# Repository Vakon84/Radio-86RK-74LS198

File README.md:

# SN74198N (K155IR13) replacement

SN74198 (K155IR13) replacement with a pair of 74LS194D

Radio-86RK, a 8080-based home computer from 1986, uses a SN74198 parallel-in, serial-out shift register to serialize pixel data for the composite video output. The part is long obsolete. Although it can still be found on eBay, etc., a fully functional replacement can easily be built from two 74LS194 shift registers. Using the 74LS194D in SOIC packages, it is possible to built a size- and pin-compatible replacement for 74198.

## Schematic and PCB layout
[Schematic](Eagle/74LS198-schematic.pdf)

[PCB layout](Eagle/74LS198-pcb.pdf)

## Bill of Materials

Device   | Package | Quantity
-------- | ------- | --------
74LS194D | SOIC-16 | 2
Capacitor 0.1uF | 0805 | 2

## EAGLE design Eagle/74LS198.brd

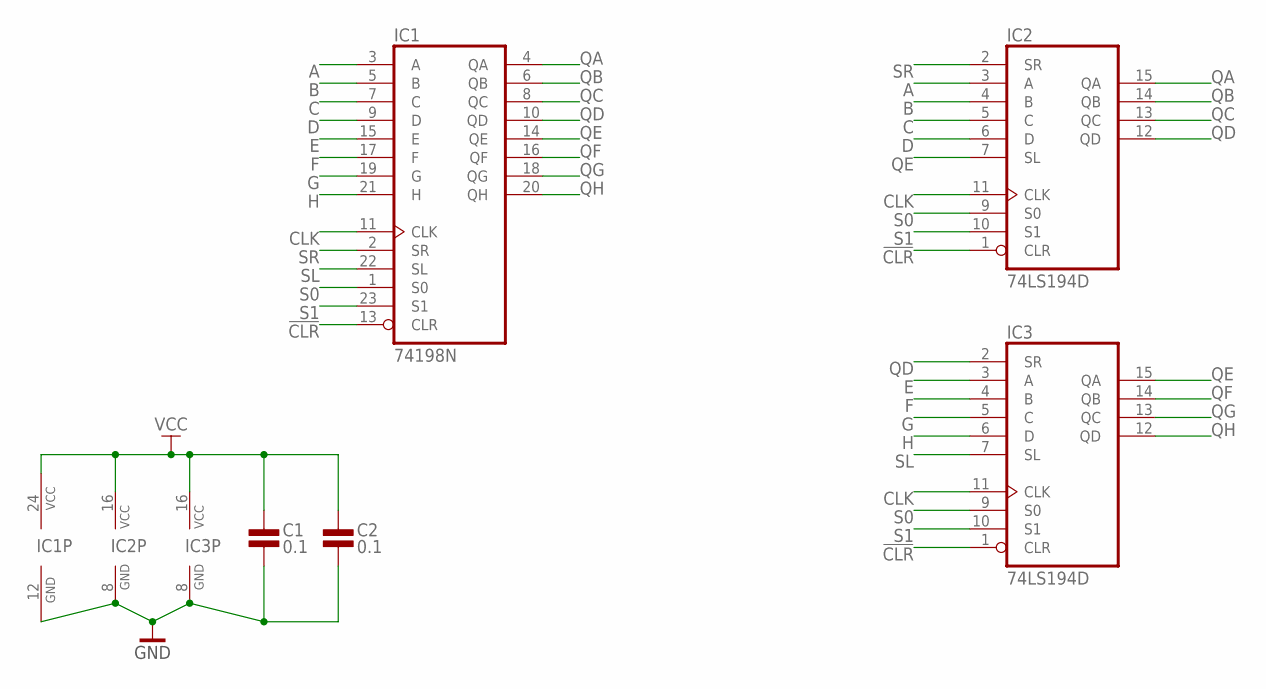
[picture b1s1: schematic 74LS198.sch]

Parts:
C1, C2: 0.1; 0805
IC1: 74198N; DIP24W
IC2, IC3: 74LS194D; SO16

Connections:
!CLR: IC1.13 (CLR), IC2.1 (CLR), IC3.1 (CLR)
A: IC1.3 (A), IC2.3 (A)
B: IC1.5 (B), IC2.4 (B)
C: IC1.7 (C), IC2.5 (C)
CLK: IC1.11 (CLK), IC2.11 (CLK), IC3.11 (CLK)
D: IC1.9 (D), IC2.6 (D)
E: IC1.15 (E), IC3.3 (A)
F: IC1.17 (F), IC3.4 (B)
G: IC1.19 (G), IC3.5 (C)
GND: C1.1, C2.1, IC1.12 (GND), IC2.8 (GND), IC3.8 (GND)
H: IC1.21 (H), IC3.6 (D)
QA: IC1.4 (QA), IC2.15 (QA)
QB: IC1.6 (QB), IC2.14 (QB)
QC: IC1.8 (QC), IC2.13 (QC)
QD: IC1.10 (QD), IC2.12 (QD), IC3.2 (SR)
QE: IC1.14 (QE), IC2.7 (SL), IC3.15 (QA)
QF: IC1.16 (QF), IC3.14 (QB)
QG: IC1.18 (QG), IC3.13 (QC)
QH: IC1.20 (QH), IC3.12 (QD)
S0: IC1.1 (S0), IC2.9 (S0), IC3.9 (S0)
S1: IC1.23 (S1), IC2.10 (S1), IC3.10 (S1)
SL: IC1.22 (SL), IC3.7 (SL)
SR: IC1.2 (SR), IC2.2 (SR)
VCC: C1.2, C2.2, IC1.24 (VCC), IC2.16 (VCC), IC3.16 (VCC)

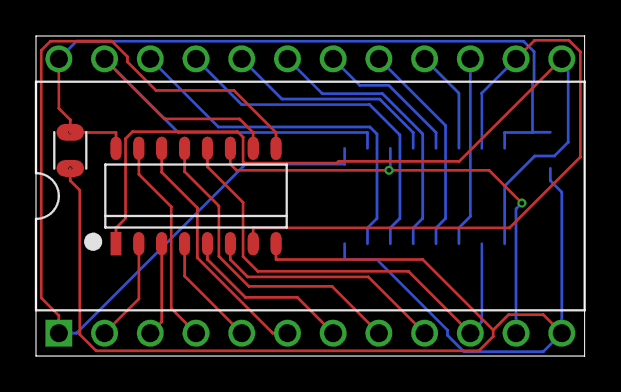
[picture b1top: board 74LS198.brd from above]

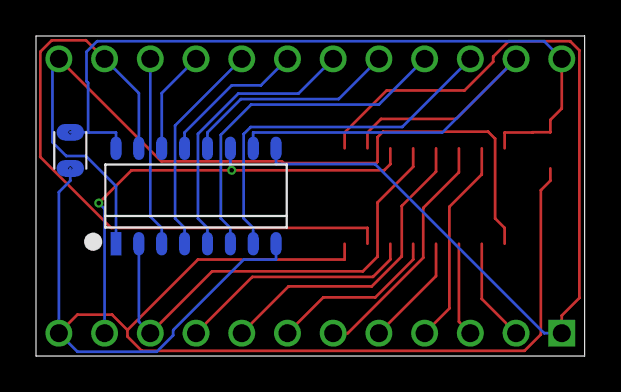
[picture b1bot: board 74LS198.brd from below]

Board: 2 copper layers, 30.5 x 17.8 mm, 5 parts (2 on the bottom side), 24 nets.
